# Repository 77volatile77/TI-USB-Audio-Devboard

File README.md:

# TI-USB-Audio-Devboard

A breadboard adapter for the PCM2906C: A USB 1.1 audio codec made by Texas Instruments. Note: the way the header pinout is defined, this board is only intended to be used *as a DAC.* However, you can choose to DNP the pull-down resistors on the VINR + VINL pins and solder jumpers onto the pad and use it that way.

# Demo
https://www.youtube.com/watch?v=z2hdiVDINO0

# Viewing source

You can either clone the project and view it on your copy of KiCad, or you can use [KiCanvas](https://kicanvas.org/) to look at the schematics on the web.

Enter the following URL onto KiCanvas: https://github.com/77volatile77/TI-USB-Audio-Devboard/tree/main/dac

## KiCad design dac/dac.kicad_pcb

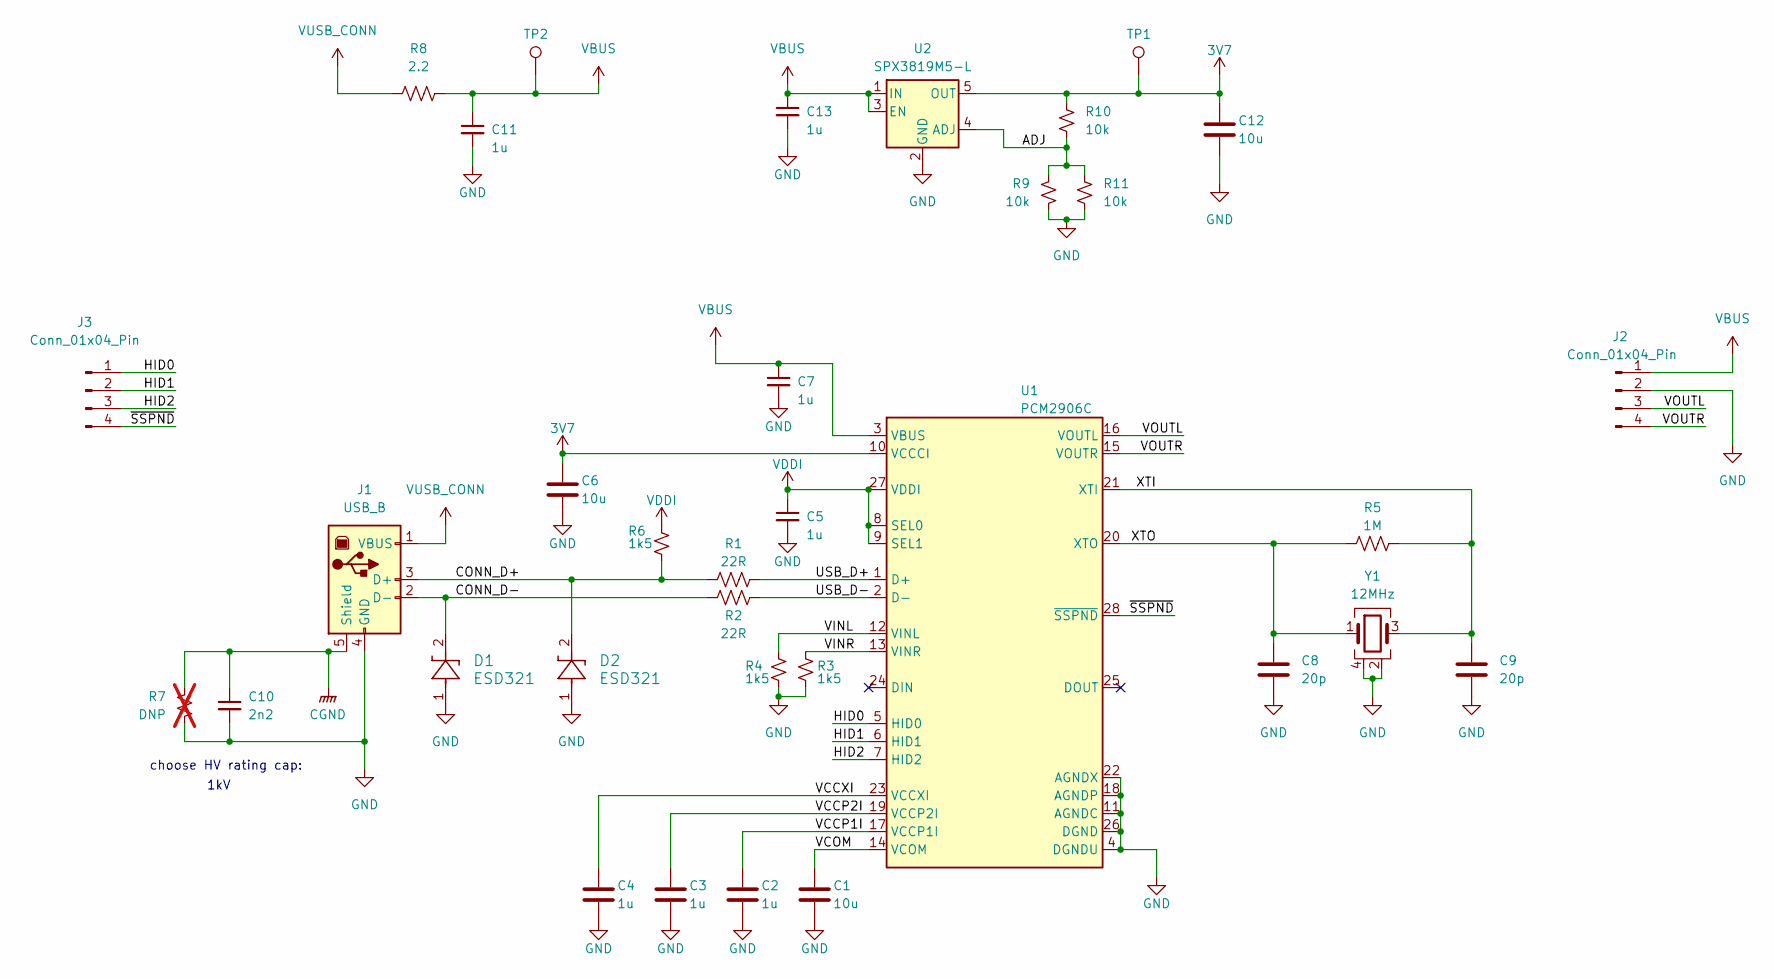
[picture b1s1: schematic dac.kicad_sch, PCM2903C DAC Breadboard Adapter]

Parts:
C1, C6, C12: 10u; C_0805_2012Metric_Pad1.18x1.45mm_HandSolder
C2, C3, C4, C5, C7, C11, C13: 1u; C_0402_1005Metric_Pad0.74x0.62mm_HandSolder
C8, C9: 20p; C_0402_1005Metric_Pad0.74x0.62mm_HandSolder
C10: 2n2; C_0805_2012Metric_Pad1.18x1.45mm_HandSolder
D1, D2: ESD321; SOT5x3_DYA_TEX-M
J1: USB_B; USB_B_OST_USB-B1HSxx_Horizontal
J2, J3: Conn_01x04_Pin; PinHeader_1x04_P2.54mm_Vertical
R1, R2: 22R; R_0402_1005Metric_Pad0.72x0.64mm_HandSolder
R3, R4, R6: 1k5; R_0402_1005Metric_Pad0.72x0.64mm_HandSolder
R5: 1M; R_0402_1005Metric_Pad0.72x0.64mm_HandSolder
R7: DNP; R_0402_1005Metric_Pad0.72x0.64mm_HandSolder; not fitted
R8: 2.2; R_0603_1608Metric_Pad0.98x0.95mm_HandSolder
R9, R10, R11: 10k; R_0402_1005Metric_Pad0.72x0.64mm_HandSolder
TP1, TP2: TestPoint; TestPoint_Pad_D1.0mm
U1: PCM2906C; SSOP-28_5.3x10.2mm_P0.65mm
U2: SPX3819M5-L; SOT-23-5
Y1: 12MHz; XTAL_ABM8-12.000MHZ-12-B1U-T

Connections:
3V7: C6.1, C12.1, R10.1, TP1.1, U1.10 (VCCCI), U2.5 (OUT)
/ADJ: R9.1, R10.2, R11.1, U2.4 (ADJ)
/CONN_D+: D2.2, J1.3 (D+), R1.1, R6.2
/CONN_D-: D1.2, J1.2 (D-), R2.1
/HID0: J3.1, U1.5 (HID0)
/HID1: J3.2, U1.6 (HID1)
/HID2: J3.3, U1.7 (HID2)
/USB_D+: R1.2, U1.1 (D+)
/USB_D-: R2.2, U1.2 (D-)
/VCCP1I: C2.1, U1.17 (VCCP1I)
/VCCP2I: C3.1, U1.19 (VCCP2I)
/VCCXI: C4.1, U1.23 (VCCXI)
/VCOM: C1.1, U1.14 (VCOM)
/VINL: R4.1, U1.12 (VINL)
/VINR: R3.1, U1.13 (VINR)
/VOUTL: J2.3, U1.16 (VOUTL)
/VOUTR: J2.4, U1.15 (VOUTR)
/XTI: C9.1, R5.2, U1.21 (XTI), Y1.3
/XTO: C8.1, R5.1, U1.20 (XTO), Y1.1
/~SSPND: J3.4, U1.28 (~SSPND)
CGND: C10.1, J1.5 (Shield), R7.1
GND: C1.2, C2.2, C3.2, C4.2, C5.2, C6.2, C7.2, C8.2, C9.2, C10.2, C11.2, C12.2, C13.2, D1.1, D2.1, J1.4 (GND), J2.2, R3.2, R4.2, R7.2, R9.2, R11.2, U1.4 (DGNDU), U1.11 (AGNDC), U1.18 (AGNDP), U1.22 (AGNDX), U1.26 (DGND), U2.2 (GND), Y1.2, Y1.4
VBUS: C7.1, C11.1, C13.1, J2.1, R8.2, TP2.1, U1.3 (VBUS), U2.1 (IN), U2.3 (EN)
VDDI: C5.1, R6.1, U1.8 (SEL0), U1.9 (SEL1), U1.27 (VDDI)
VUSB_CONN: J1.1 (VBUS), R8.1

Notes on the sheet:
choose HV rating cap:
1kV

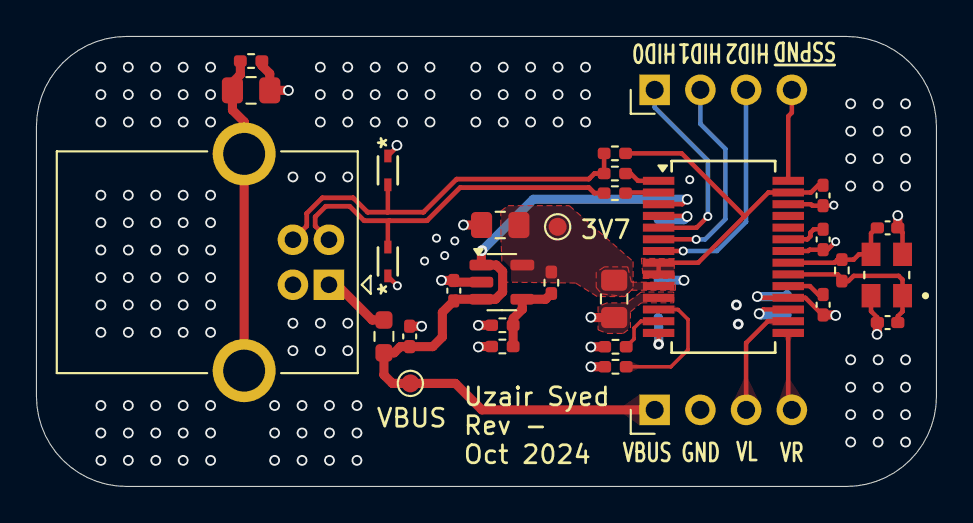
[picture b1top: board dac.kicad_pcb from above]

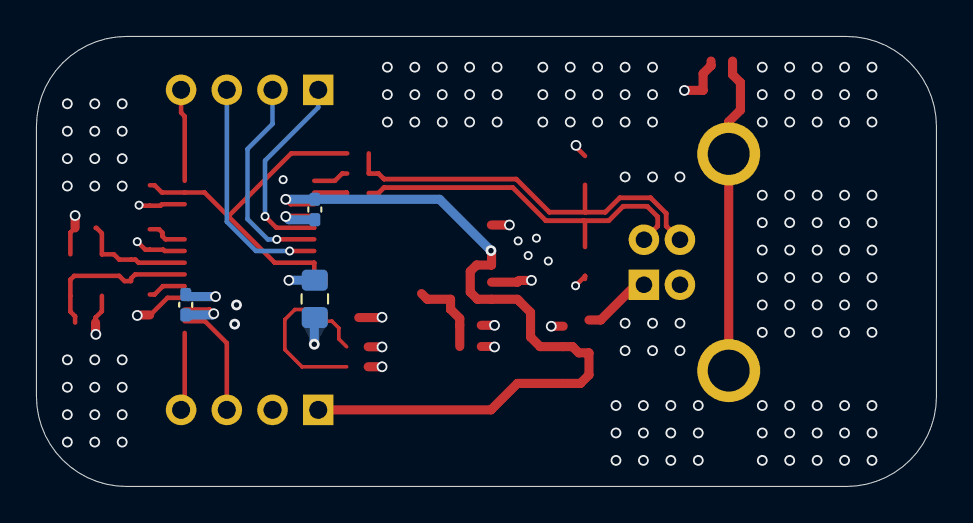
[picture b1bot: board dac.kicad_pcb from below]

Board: 4 copper layers, 50.0 x 25.0 mm, 34 parts (3 on the bottom side), 25 nets.

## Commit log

2024-10-07 finished component placement, need to figure out header pinouts
2024-10-07 added 3D bodies for ESD diodes
2024-10-07 README changes, changed gitconfig email lol
2024-10-07 Update README.md
    add pictures to readme
2024-10-07 readme updates
2024-10-07 changed README to reflect the fact that you can still use the ADC part of the codec.
2024-10-07 started layout
2024-10-08 layout is complete
2024-10-08 added stitching, redid 3d models
2024-10-08 added teardrops & extra stitching
2024-10-09 backups
2024-10-09 labeled headers and test points
2024-10-10 final cleanup
2024-10-10 add output files
2024-10-11 changed U1 name to correct chip PCM2906C
